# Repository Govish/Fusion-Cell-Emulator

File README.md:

# Fusion-Cell-Emulator
 10s Lithium stack emulator that supports 720mA total balance current and simulated cell voltage adjustment

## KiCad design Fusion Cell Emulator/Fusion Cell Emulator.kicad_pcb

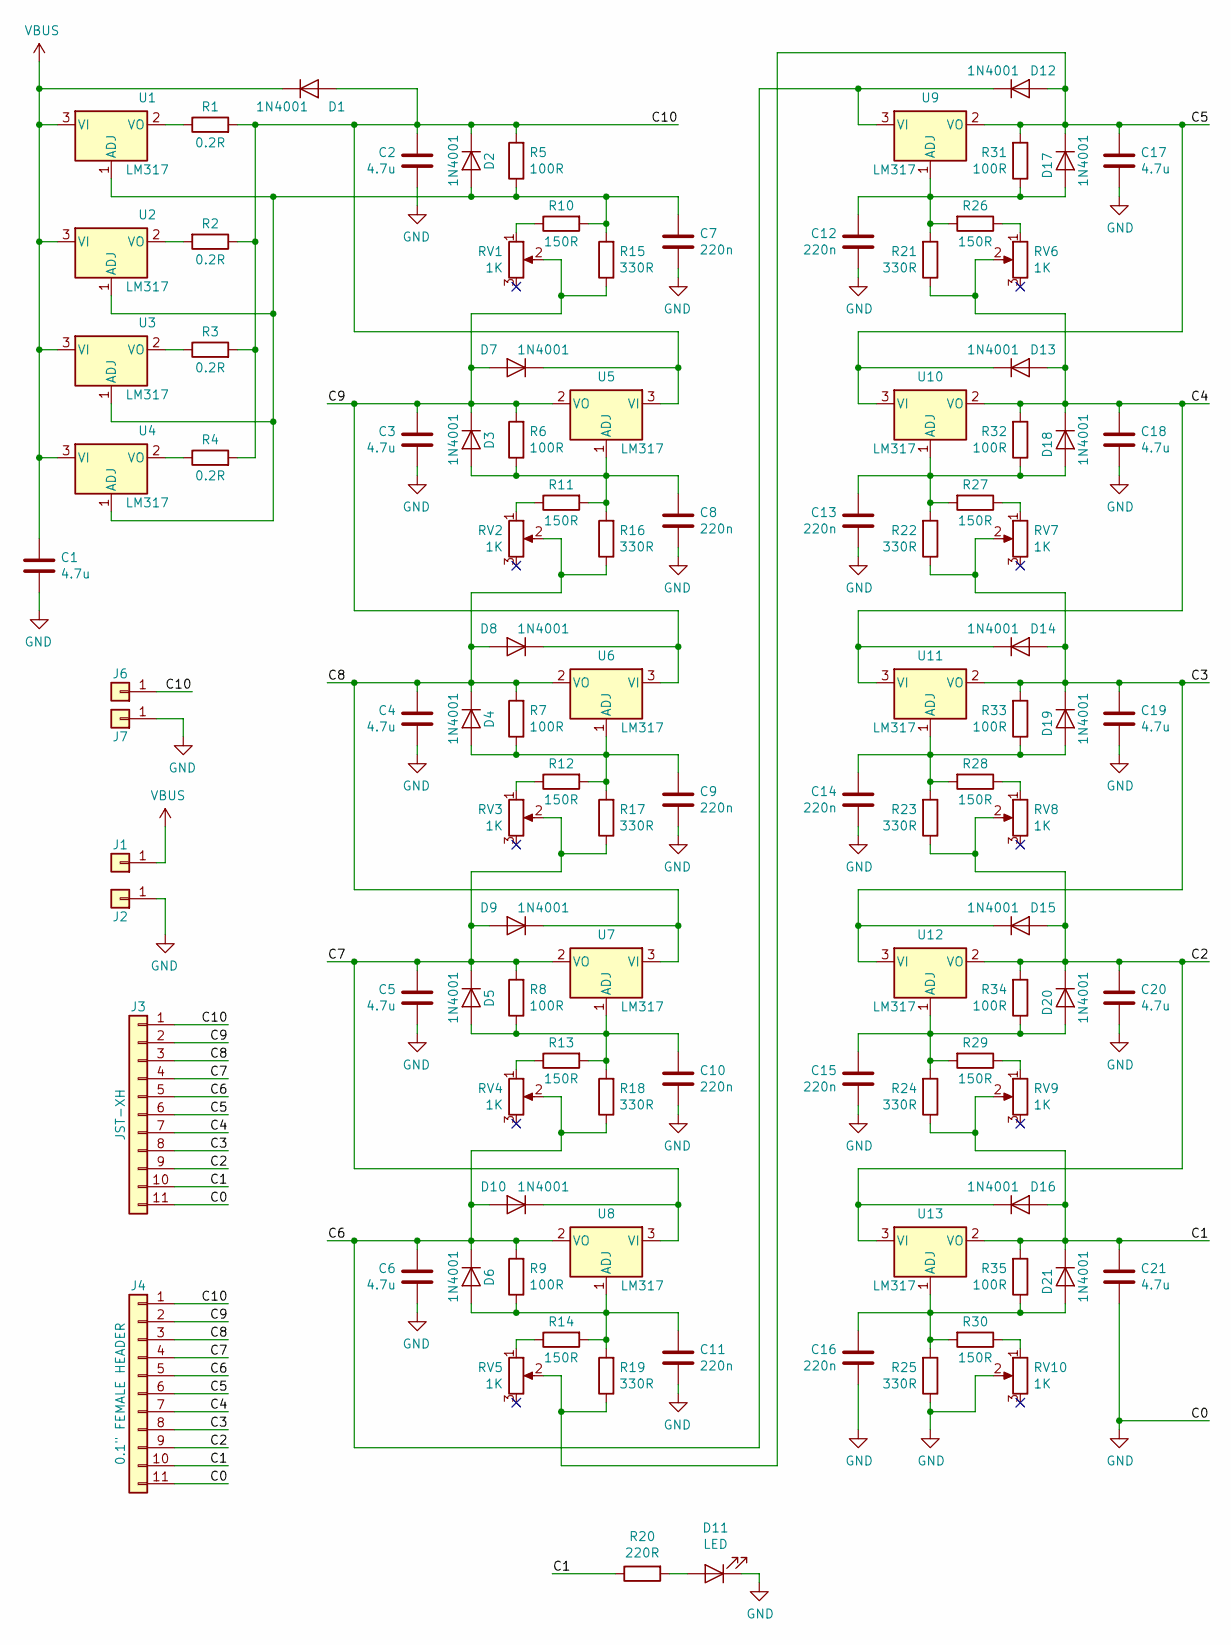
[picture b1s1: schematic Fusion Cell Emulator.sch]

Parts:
C1, C2, C3, C4, C5, C6, C17, C18, C19, C20, C21: 4.7u; CP_Radial_D5.0mm_P2.00mm
C7, C8, C9, C10, C11, C12, C13, C14, C15, C16: 220n; C_Rect_L7.5mm_W2.5mm_P5.08mm
D1, D2, D3, D4, D5, D6, D7, D8, D9, D10, D12, D13, D14, D15, D16, D17, D18, D19, D20, D21: 1N4001; D_DO-41_SOD81_P10.16mm_Horizontal
D11: LED; LED_D5.0mm
J1, J6: BINDING_POST_RED; Conn_BindingPost_Red
J2, J7: BINDING_POST_BLACK; Conn_BindingPost_Black
J3: JST-XH; JST_XH_B11B-XH-A_1x11_P2.50mm_Vertical
J4: 0.1\" FEMALE HEADER; PinSocket_1x11_P2.54mm_Vertical
R1, R2, R3, R4: 0.2R; R_Axial_DIN0207_L6.3mm_D2.5mm_P10.16mm_Horizontal
R5, R6, R7, R8, R9, R31, R32, R33, R34, R35: 100R; R_Axial_DIN0207_L6.3mm_D2.5mm_P10.16mm_Horizontal
R10, R11, R12, R13, R14, R26, R27, R28, R29, R30: 150R; R_Axial_DIN0207_L6.3mm_D2.5mm_P10.16mm_Horizontal
R15, R16, R17, R18, R19, R21, R22, R23, R24, R25: 330R; R_Axial_DIN0207_L6.3mm_D2.5mm_P10.16mm_Horizontal
R20: 220R; R_Axial_DIN0207_L6.3mm_D2.5mm_P10.16mm_Horizontal
RV1, RV2, RV3, RV4, RV5, RV6, RV7, RV8, RV9, RV10: 1K; Potentiometer-reverse-mount-160
U1, U2, U3, U4, U5, U6, U7, U8, U9, U10, U11, U12, U13: LM317; TO-220-3-AAVID-5932

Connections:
/C1: C21.1, D16.2 (A), D21.1 (K), J3.10, J4.10, R20.1, R24.1, R35.2, RV9.2, U13.2 (VO)
/C2: C20.1, D15.2 (A), D16.1 (K), D20.1 (K), J3.9, J4.9, R23.1, R34.2, RV8.2, U12.2 (VO), U13.3 (VI)
/C3: C19.1, D14.2 (A), D15.1 (K), D19.1 (K), J3.8, J4.8, R22.1, R33.2, RV7.2, U11.2 (VO), U12.3 (VI)
/C4: C18.1, D13.2 (A), D14.1 (K), D18.1 (K), J3.7, J4.7, R21.1, R32.2, RV6.2, U10.2 (VO), U11.3 (VI)
/C5: C17.1, D12.2 (A), D13.1 (K), D17.1 (K), J3.6, J4.6, R19.1, R31.2, RV5.2, U9.2 (VO), U10.3 (VI)
/C6: C6.1, D6.1 (K), D10.2 (A), D12.1 (K), J3.5, J4.5, R9.2, R18.1, RV4.2, U8.2 (VO), U9.3 (VI)
/C7: C5.1, D5.1 (K), D9.2 (A), D10.1 (K), J3.4, J4.4, R8.2, R17.1, RV3.2, U7.2 (VO), U8.3 (VI)
/C8: C4.1, D4.1 (K), D8.2 (A), D9.1 (K), J3.3, J4.3, R7.2, R16.1, RV2.2, U6.2 (VO), U7.3 (VI)
/C9: C3.1, D3.1 (K), D7.2 (A), D8.1 (K), J3.2, J4.2, R6.2, R15.1, RV1.2, U5.2 (VO), U6.3 (VI)
/C10: C2.1, D1.2 (A), D2.1 (K), D7.1 (K), J3.1, J4.1, J6.1, R1.2, R2.1, R3.2, R4.2, R5.2, U5.3 (VI)
GND: C1.2, C2.2, C3.2, C4.2, C5.2, C6.2, C7.1, C8.1, C9.1, C10.1, C11.1, C12.1, C13.1, C14.1, C15.1, C16.1, C17.2, C18.2, C19.2, C20.2, C21.2, D11.1 (K), J2.1, J3.11, J4.11, J7.1, R25.1, RV10.2
unnamed: C7.2, D2.2 (A), R5.1, R10.2, R15.2, U1.1 (ADJ), U2.1 (ADJ), U3.1 (ADJ), U4.1 (ADJ)
unnamed: C8.2, D3.2 (A), R6.1, R11.2, R16.2, U5.1 (ADJ)
unnamed: C9.2, D4.2 (A), R7.1, R12.2, R17.2, U6.1 (ADJ)
unnamed: C10.2, D5.2 (A), R8.1, R13.2, R18.2, U7.1 (ADJ)
unnamed: C11.2, D6.2 (A), R9.1, R14.2, R19.2, U8.1 (ADJ)
unnamed: C12.2, D17.2 (A), R21.2, R26.2, R31.1, U9.1 (ADJ)
unnamed: C13.2, D18.2 (A), R22.2, R27.2, R32.1, U10.1 (ADJ)
unnamed: C14.2, D19.2 (A), R23.2, R28.2, R33.1, U11.1 (ADJ)
unnamed: C15.2, D20.2 (A), R24.2, R29.2, R34.1, U12.1 (ADJ)
unnamed: C16.2, D21.2 (A), R25.2, R30.2, R35.1, U13.1 (ADJ)
unnamed: D11.2 (A), R20.2
unnamed: R1.1, U1.2 (VO)
unnamed: R2.2, U2.2 (VO)
unnamed: R3.1, U3.2 (VO)
unnamed: R4.1, U4.2 (VO)
unnamed: R10.1, RV1.1
unnamed: R11.1, RV2.1
unnamed: R12.1, RV3.1
unnamed: R13.1, RV4.1
unnamed: R14.1, RV5.1
unnamed: R26.1, RV6.1
unnamed: R27.1, RV7.1
unnamed: R28.1, RV8.1
unnamed: R29.1, RV9.1
unnamed: R30.1, RV10.1
VBUS: C1.1, D1.1 (K), J1.1, U1.3 (VI), U2.3 (VI), U3.3 (VI), U4.3 (VI)

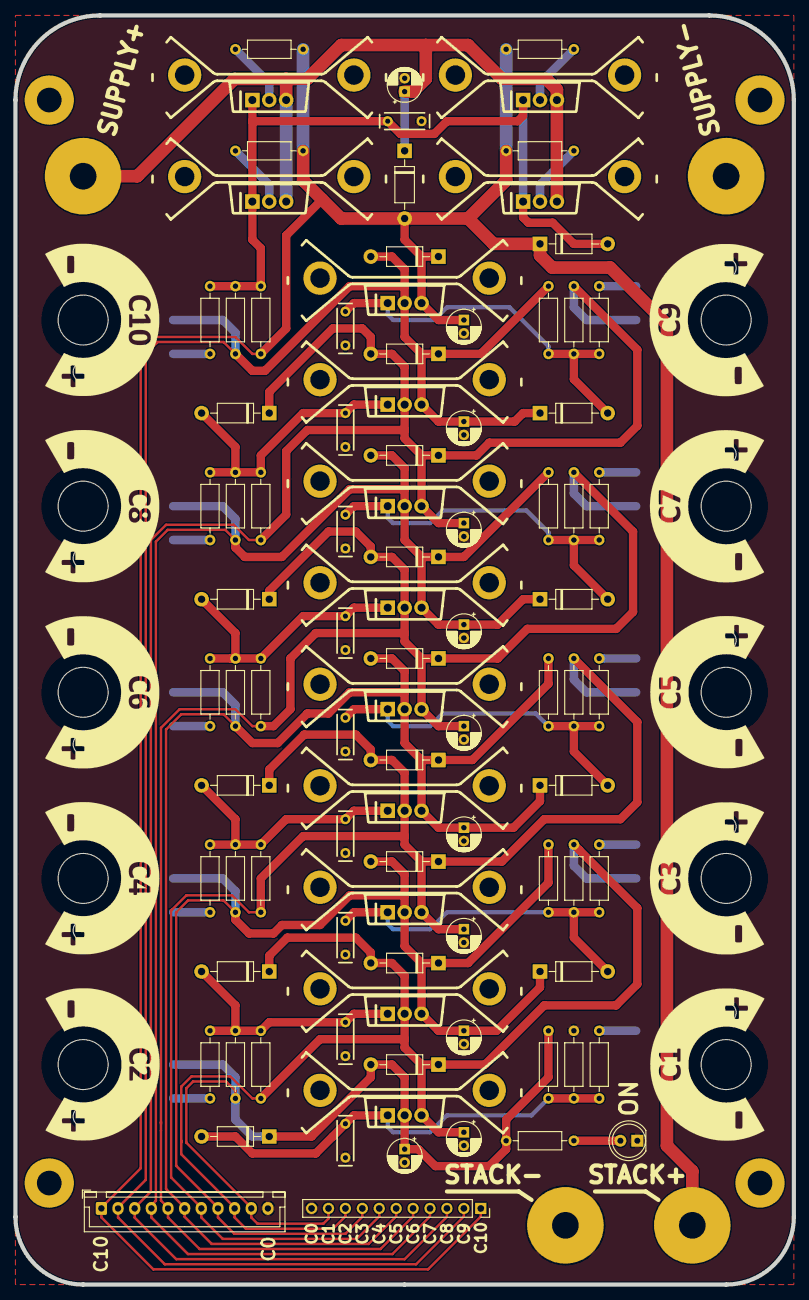
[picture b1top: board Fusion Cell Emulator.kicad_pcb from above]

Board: 2 copper layers, 116.8 x 190.5 mm, 106 parts (0 on the bottom side), 37 nets.

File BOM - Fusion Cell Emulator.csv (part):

"Source:","D:\Documents\Projects\Fusion Cell Emulator\Fusion Cell Emulator\Fusion Cell Emulator.sch"
"Date:","10/11/2019 12:42:54 AM"
"Tool:","Eeschema (5.1.4)-1"
"Generator:","C:\Program Files\KiCad\bin\scripting\plugins/bom_csv_grouped_by_value.py"
"Component Count:","106"

"Individual Components:"

"Item","Qty","Reference(s)","Value","LibPart","Footprint","Datasheet"
"","","C1","4.7u","Device:C","Capacitor_THT:CP_Radial_D5.0mm_P2.00mm","~"
"","","C2","4.7u","Device:C","Capacitor_THT:CP_Radial_D5.0mm_P2.00mm","~"
"","","C3","4.7u","Device:C","Capacitor_THT:CP_Radial_D5.0mm_P2.00mm","~"
"","","C4","4.7u","Device:C","Capacitor_THT:CP_Radial_D5.0mm_P2.00mm","~"
"","","C5","4.7u","Device:C","Capacitor_THT:CP_Radial_D5.0mm_P2.00mm","~"
"","","C6","4.7u","Device:C","Capacitor_THT:CP_Radial_D5.0mm_P2.00mm","~"
"","","C7","220n","Device:C","Custom-RLC:C_Rect_L7.5mm_W2.5mm_P5.08mm","~"
"","","C8","220n","Device:C","Custom-RLC:C_Rect_L7.5mm_W2.5mm_P5.08mm","~"
"","","C9","220n","Device:C","Custom-RLC:C_Rect_L7.5mm_W2.5mm_P5.08mm","~"
"","","C10","220n","Device:C","Custom-RLC:C_Rect_L7.5mm_W2.5mm_P5.08mm","~"
"","","C11","220n","Device:C","Custom-RLC:C_Rect_L7.5mm_W2.5mm_P5.08mm","~"
"","","C12","220n","Device:C","Custom-RLC:C_Rect_L7.5mm_W2.5mm_P5.08mm","~"
"","","C13","220n","Device:C","Custom-RLC:C_Rect_L7.5mm_W2.5mm_P5.08mm","~"
"","","C14","220n","Device:C","Custom-RLC:C_Rect_L7.5mm_W2.5mm_P5.08mm","~"
"","","C15","220n","Device:C","Custom-RLC:C_Rect_L7.5mm_W2.5mm_P5.08mm","~"
"","","C16","220n","Device:C","Custom-RLC:C_Rect_L7.5mm_W2.5mm_P5.08mm","~"
"","","C17","4.7u","Device:C","Capacitor_THT:CP_Radial_D5.0mm_P2.00mm","~"
"","","C18","4.7u","Device:C","Capacitor_THT:CP_Radial_D5.0mm_P2.00mm","~"
"","","C19","4.7u","Device:C","Capacitor_THT:CP_Radial_D5.0mm_P2.00mm","~"
"","","C20","4.7u","Device:C","Capacitor_THT:CP_Radial_D5.0mm_P2.00mm","~"
"","","C21","4.7u","Device:C","Capacitor_THT:CP_Radial_D5.0mm_P2.00mm","~"
"","","D1","1N4001","Device:D","Diode_THT:D_DO-41_SOD81_P10.16mm_Horizontal","~"
"","","D2","1N4001","Device:D","Diode_THT:D_DO-41_SOD81_P10.16mm_Horizontal","~"
"","","D3","1N4001","Device:D","Diode_THT:D_DO-41_SOD81_P10.16mm_Horizontal","~"
"","","D4","1N4001","Device:D","Diode_THT:D_DO-41_SOD81_P10.16mm_Horizontal","~"
"","","D5","1N4001","Device:D","Diode_THT:D_DO-41_SOD81_P10.16mm_Horizontal","~"
"","","D6","1N4001","Device:D","Diode_THT:D_DO-41_SOD81_P10.16mm_Horizontal","~"
"","","D7","1N4001","Device:D","Diode_THT:D_DO-41_SOD81_P10.16mm_Horizontal","~"
"","","D8","1N4001","Device:D","Diode_THT:D_DO-41_SOD81_P10.16mm_Horizontal","~"
"","","D9","1N4001","Device:D","Diode_THT:D_DO-41_SOD81_P10.16mm_Horizontal","~"
"","","D10","1N4001","Device:D","Diode_THT:D_DO-41_SOD81_P10.16mm_Horizontal","~"
"","","D11","LED","Device:LED","LED_THT:LED_D5.0mm","~"
"","","D12","1N4001","Device:D","Diode_THT:D_DO-41_SOD81_P10.16mm_Horizontal","~"
"","","D13","1N4001","Device:D","Diode_THT:D_DO-41_SOD81_P10.16mm_Horizontal","~"
"","","D14","1N4001","Device:D","Diode_THT:D_DO-41_SOD81_P10.16mm_Horizontal","~"
"","","D15","1N4001","Device:D","Diode_THT:D_DO-41_SOD81_P10.16mm_Horizontal","~"
"","","D16","1N4001","Device:D","Diode_THT:D_DO-41_SOD81_P10.16mm_Horizontal","~"
"","","D17","1N4001","Device:D","Diode_THT:D_DO-41_SOD81_P10.16mm_Horizontal","~"
"","","D18","1N4001","Device:D","Diode_THT:D_DO-41_SOD81_P10.16mm_Horizontal","~"
"","","D19","1N4001","Device:D","Diode_THT:D_DO-41_SOD81_P10.16mm_Horizontal","~"
"","","D20","1N4001","Device:D","Diode_THT:D_DO-41_SOD81_P10.16mm_Horizontal","~"
"","","D21","1N4001","Device:D","Diode_THT:D_DO-41_SOD81_P10.16mm_Horizontal","~"
"","","J1","BINDING_POST_RED","Connector_Generic:Conn_01x01","Custom-Electromechanical:Conn_BindingPost_Red","~"
"","","J2","BINDING_POST_BLACK","Connector_Generic:Conn_01x01","Custom-Electromechanical:Conn_BindingPost_Black","~"
"","","J3","JST-XH","Connector_Generic:Conn_01x11","Connector_JST:JST_XH_B11B-XH-A_1x11_P2.50mm_Vertical","~"
"","","J4","0.1"" FEMALE HEADER","Connector_Generic:Conn_01x11","Connector_PinSocket_2.54mm:PinSocket_1x11_P2.54mm_Vertical","~"
"","","J6","BINDING_POST_RED","Connector_Generic:Conn_01x01","Custom-Electromechanical:Conn_BindingPost_Red","~"
"","","J7","BINDING_POST_BLACK","Connector_Generic:Conn_01x01","Custom-Electromechanical:Conn_BindingPost_Black","~"
"","","R1","0.2R","Device:R","Resistor_THT:R_Axial_DIN0207_L6.3mm_D2.5mm_P10.16mm_Horizontal","~"
"","","R2","0.2R","Device:R","Resistor_THT:R_Axial_DIN0207_L6.3mm_D2.5mm_P10.16mm_Horizontal","~"
"","","R3","0.2R","Device:R","Resistor_THT:R_Axial_DIN0207_L6.3mm_D2.5mm_P10.16mm_Horizontal","~"
"","","R4","0.2R","Device:R","Resistor_THT:R_Axial_DIN0207_L6.3mm_D2.5mm_P10.16mm_Horizontal","~"
"","","R5","100R","Device:R","Resistor_THT:R_Axial_DIN0207_L6.3mm_D2.5mm_P10.16mm_Horizontal","~"
"","","R6","100R","Device:R","Resistor_THT:R_Axial_DIN0207_L6.3mm_D2.5mm_P10.16mm_Horizontal","~"
"","","R7","100R","Device:R","Resistor_THT:R_Axial_DIN0207_L6.3mm_D2.5mm_P10.16mm_Horizontal","~"
"","","R8","100R","Device:R","Resistor_THT:R_Axial_DIN0207_L6.3mm_D2.5mm_P10.16mm_Horizontal","~"
"","","R9","100R","Device:R","Resistor_THT:R_Axial_DIN0207_L6.3mm_D2.5mm_P10.16mm_Horizontal","~"
"","","R10","150R","Device:R","Resistor_THT:R_Axial_DIN0207_L6.3mm_D2.5mm_P10.16mm_Horizontal","~"
"","","R11","150R","Device:R","Resistor_THT:R_Axial_DIN0207_L6.3mm_D2.5mm_P10.16mm_Horizontal","~"
"","","R12","150R","Device:R","Resistor_THT:R_Axial_DIN0207_L6.3mm_D2.5mm_P10.16mm_Horizontal","~"
"","","R13","150R","Device:R","Resistor_THT:R_Axial_DIN0207_L6.3mm_D2.5mm_P10.16mm_Horizontal","~"
"","","R14","150R","Device:R","Resistor_THT:R_Axial_DIN0207_L6.3mm_D2.5mm_P10.16mm_Horizontal","~"
"","","R15","330R","Device:R","Resistor_THT:R_Axial_DIN0207_L6.3mm_D2.5mm_P10.16mm_Horizontal","~"
"","","R16","330R","Device:R","Resistor_THT:R_Axial_DIN0207_L6.3mm_D2.5mm_P10.16mm_Horizontal","~"
"","","R17","330R","Device:R","Resistor_THT:R_Axial_DIN0207_L6.3mm_D2.5mm_P10.16mm_Horizontal","~"
"","","R18","330R","Device:R","Resistor_THT:R_Axial_DIN0207_L6.3mm_D2.5mm_P10.16mm_Horizontal","~"
"","","R19","330R","Device:R","Resistor_THT:R_Axial_DIN0207_L6.3mm_D2.5mm_P10.16mm_Horizontal","~"
"","","R20","220R","Device:R","Resistor_THT:R_Axial_DIN0207_L6.3mm_D2.5mm_P10.16mm_Horizontal","~"
"","","R21","330R","Device:R","Resistor_THT:R_Axial_DIN0207_L6.3mm_D2.5mm_P10.16mm_Horizontal","~"
"","","R22","330R","Device:R","Resistor_THT:R_Axial_DIN0207_L6.3mm_D2.5mm_P10.16mm_Horizontal","~"
"","","R23","330R","Device:R","Resistor_THT:R_Axial_DIN0207_L6.3mm_D2.5mm_P10.16mm_Horizontal","~"
"","","R24","330R","Device:R","Resistor_THT:R_Axial_DIN0207_L6.3mm_D2.5mm_P10.16mm_Horizontal","~"
"","","R25","330R","Device:R","Resistor_THT:R_Axial_DIN0207_L6.3mm_D2.5mm_P10.16mm_Horizontal","~"
"","","R26","150R","Device:R","Resistor_THT:R_Axial_DIN0207_L6.3mm_D2.5mm_P10.16mm_Horizontal","~"
"","","R27","150R","Device:R","Resistor_THT:R_Axial_DIN0207_L6.3mm_D2.5mm_P10.16mm_Horizontal","~"
"","","R28","150R","Device:R","Resistor_THT:R_Axial_DIN0207_L6.3mm_D2.5mm_P10.16mm_Horizontal","~"
"","","R29","150R","Device:R","Resistor_THT:R_Axial_DIN0207_L6.3mm_D2.5mm_P10.16mm_Horizontal","~"
"","","R30","150R","Device:R","Resistor_THT:R_Axial_DIN0207_L6.3mm_D2.5mm_P10.16mm_Horizontal","~"
"","","R31","100R","Device:R","Resistor_THT:R_Axial_DIN0207_L6.3mm_D2.5mm_P10.16mm_Horizontal","~"
"","","R32","100R","Device:R","Resistor_THT:R_Axial_DIN0207_L6.3mm_D2.5mm_P10.16mm_Horizontal","~"
"","","R33","100R","Device:R","Resistor_THT:R_Axial_DIN0207_L6.3mm_D2.5mm_P10.16mm_Horizontal","~"
"","","R34","100R","Device:R","Resistor_THT:R_Axial_DIN0207_L6.3mm_D2.5mm_P10.16mm_Horizontal","~"
"","","R35","100R","Device:R","Resistor_THT:R_Axial_DIN0207_L6.3mm_D2.5mm_P10.16mm_Horizontal","~"
"","","RV1","1K","Device:R_POT","Custom-Electromechanical:Potentiometer-reverse-mount-160","~"
"","","RV2","1K","Device:R_POT","Custom-Electromechanical:Potentiometer-reverse-mount-160","~"
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
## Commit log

2019-10-13 Fixing silk screen and updating gerbers
2019-10-13 Create LICENSE
2019-10-24 Fixed JST orietation and Final Gerbers
2019-12-01 Adding pics!
2020-01-23 Updated Pics, added shunt bodge resistor note
